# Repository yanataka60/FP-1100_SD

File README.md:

# CASIO FP-1100にSD-Cardとのロード、セーブ機能

　CASIO FP-1100でCMTの代わりにSD-CARDからロード、セーブを実現するものです。

　FP-1000は所有していないので試していませんが、動作すると思います。

　SDから読み込めるCMTのファイル形式はEMUで一般的なWAV、CASには対応していません。bugfire2009さんのDumpListEditorを使ってバイナリ形式に変換したものを使います。

　機械語 -> 各モデル固有ヘッダ付きBINファイル、拡張子は.bin

　BASIC -> BASファイル、拡張子は.bas

　CMTからの読み込み実行に数分掛かっていたゲームも数十秒で実行できます。

　ただし、CMT用プログラムのすべてがSD対応となるわけではありません。特に市販ゲームはCMT読み込みに独自ルーチンを使っているものもあるため、SD対応は不明です。

　なお、Arduino、ROMへ書き込むための機器が別途必要となります。

## 回路図
　KiCadフォルダ内のFP-1100_SD.PDFを参照してください。

[回路図](https://github.com/yanataka60/FP-1100_SD/blob/main/Kicad/FP-1100_SD.PDF)

## 部品
|番号|品名|数量|備考|
| ------------ | ------------ | ------------ | ------------ |
||J3,J4のいずれか|||
|J3|Micro_SD_Card_Kit|1|秋月電子通商 AE-microSD-LLCNV (注1)|
|J4|MicroSD Card Adapter|1|Arduino等に使われる5V電源に対応したもの(注2)|
|U1-U3|74LS04|3||
|U4-U5|74LS02|2||
|U6-U8|74LS30|3||
|U10|8255|1||
|U11|Arduino_Pro_Mini_5V|1|Atmega328版を使用 168版は不可。(注3)|
|U12|74LS32|1||
|U13|74LS244|1||
|U14|ROM 27256/29C256又は27512/27C512相当品|1|入手しやすいものでOK、28C256は不可|
|C1-C10,C12,C13|積層セラミックコンデンサ 0.1uF|12||
|C11|電解コンデンサ 16v100uF|1||
|S1|3Pin ピンヘッダーとジャンパーピン又は3Pスライドスイッチ|1|秋月電子通商 SS12D01G4など|

### 注1)秋月電子通商　AE-microSD-LLCNVのJ1ジャンパはショートしてください。

### 注2)MicroSD Card Adapterを使う場合

J4に取り付けます。

MicroSD Card Adapterについているピンヘッダを除去してハンダ付けするのが一番確実ですが、J2の穴にMicroSD Card Adapterをぴったりと押しつけ、裏から多めにハンダを流し込むことでハンダ付けをする方法もあります。なお、この方法の時にはしっかりハンダ付けが出来たかテスターで導通を確認しておいた方が安心です。

ハンダ付けに自信のない方はJ1の秋月電子通商　AE-microSD-LLCNVをお使いください。AE-microSD-LLCNVならパワーLED、アクセスLEDが付いています。

### 注3)Arduino Pro MiniはA4、A5ピンも使っています。

## FP-1100_SDをスロットに入れずに外付けとして使いたい場合のみ
　J2ピンヘッダを取り付けます。また、スロットからケーブルを引き出す基板が必要ですのでFP-1100_SD基板がもう一枚必要です。

|番号|品名|数量|備考|
| ------------ | ------------ | ------------ | ------------ |
|J2|2x25Pinコネクタ|1|秋月電子通商 PH-2x40SGなど|
||FP-1100_SD基板|1||
||2.54mmピッチ2x25Pinフラットケーブル|1|FP-1100の拡張スロットは2x28Pinですが、2x25Pinが使えます|

## 取り付け
　FP-1100本体後ろのスロットに挿入します。

　スロットにガイド等が無いためスロットの奥を覗き込みながら挿入します。

　基板の下に10～12mmの隙間が空くようにネジやスペーサーなどを取り付け、カードエッジコネクタと高さを合わせると挿入しやすくなります。

　外すときには基板のねじ穴にドライバー等を差し込んでひねるようにすれば取り外しやすいです。

　STLフォルダに基板を載せられるトレイの3Dデータを置いたので出力して使うと抜き差しが楽になります。

　標準はSLOT0ですが、SLOT1で使うときは起動後にSLコマンドでSLOT1を指定してください。

### FP-1100_SDをスロットに入れずに外付けとしてフラットケーブルによる接続
　J2コネクタ1Pinを示す基板上の△印にフラットケーブルの1Pinを示す△印を合わせてフラットケーブルを挿入します。

　FP-1100の拡張スロットは2x28Pinですが、2x25Pinフラットケーブルが使えます。

.JPG)
.JPG)
.JPG)

## ROMへの書込み
　Z80フォルダ内のRAMPACK1.binをROMライター(TL866II Plus等)を使って27256又は27512に書き込みます。

　実際に使用しているのは16KByte分(16Kx8)です。

　FP-1100_SDのROMはFP-1100からはRAMパックとして扱われます。(FP-1100から書き込みはできません。)

　本物のRAMパック、ROMパックともハードウェア的には併用可能なはずですが、現物を所有していないため動作検証は行っていません。

### 2025.8.12 FP-1100_SD以外のPACKをSLOTに挿入して同時に使用している場合にSDにアクセスできなくなるバグを発見しました。
　現在バージョンは修正済みですが、旧バージョンROMの方はZ80フォルダ内のPATCH.binをSDにコピーし、SDF8(SDE8)を実行直後にSDアクセスメニューに入り、読み込み実行すれば修正されます。

## RAMPACK1.binに登録されているファイル
　RAMPACK1.binに登録されているファイルは次の4つになります。

|ファイル名|種類|
| ------------ | ------------ |
|SDF8|BASIC|
|SDE8|BASIC|
|BOOTF8|BINARY|
|BOOTE8|BINARY|

　また、RAMPACK1.binへのファイル登録はTAKEDAさんのEMU eFP-1100で行っており、fp1100.exeと同じフォルダに置くことでeFP-1100からは「PACK0:」として読み書き出来ます。

## Arduinoプログラム
　Arduino IDEを使ってArduinoフォルダのFP-1100_SDフォルダ内FP-1100_SD.inoを書き込みます。

　SdFatライブラリを使用しているのでArduino IDEメニューのライブラリの管理からライブラリマネージャを立ち上げて「SdFat」をインストールしてください。

　「SdFat」で検索すれば見つかります。「SdFat」と「SdFat - Adafruit Fork」が見つかりますが「SdFat」のほうを使っています。

注)Arduinoを基板に直付けしている場合、Arduinoプログラムを書き込むときは、FP-1100本体とは接続を外し、U3 74LS04を外したうえで書き込んでください。

## SD-CARD
　出来れば8GB以下のSDカードを用意してください。

　ArduinoのSdFatライブラリは、SD規格(最大2GB)、SDHC規格(2GB～32GB)に対応していますが、SDXC規格(32GB～2TB)には対応していません。

　また、SDHC規格のSDカードであっても32GB、16GBは相性により動作しないものがあるようです。

　FAT16又はFAT32が認識できます。NTFSは認識できません。

## 操作方法
　起動直後に「RUN"PACK0:SDF8"」を実行してSDアクセスルーチンの読込、初期化の実行を行います。

　SDアクセスルーチンをF800h～FFFChに読み込む「SDF8」とE800h～EFF2hに読み込む「SDE8」の２種類を用意していますが、基本的には「SDF8」を使い、F000h～FFFFhへプログラムをロードしたいときだけ「SDE8」を使ってください。

　「SDE8」を使うときは、「RUN"PACK0:SDE8"」を実行します。

　SDアクセスメニューを表示するにはCALL&HF800(CALL&HE800)を実行しますが、F7ファンクションキーに登録してありますのでF7ファンクションキーを押しても大丈夫です。

#### 扱えるファイル
bugfire2009さんのDumpListEditorを使ってバイナリ形式に変換したものを使います。

扱う機種をFP-1100に変更したうえで変換します。

##### 機械語 -> 「BINファイル書出し(各モデル固有ヘッダ付き)」で保存、拡張子は.bin

##### BASIC -> 「BASファイル書出し」で保存、拡張子は.bas

### コマンド
　コマンド入力時にBSキー又は左カーソルキーで直前に入力した文字を訂正できます。

　CLR、HOME、上・下・右カーソルキーは画面が乱れるだけで入力文字の訂正は出来ません。

#### 2025.8.12 BASICプログラムを実行した後にSDアクセスメニューを実行するとコマンドを入力できなくなる場合があるようです。
　原因を調査中ですが、回避方法は以下になります。

　コマンドが入力できない状態の時はBREAKキーを押すことでBASICに戻れます。

　LISTコマンドを一回実行してください。途中でBREAKしても大丈夫です。これでSDアクセスメニューを実行しても入力できる状態に戻ります。

#### SD[RETURN]又はSD 文字列[RETURN]
　文字列を入力せずにSD[RETURN]のみ入力するとSD-CARDルートディレクトリにあるファイルの一覧を表示します。

　文字列を付けて入力すればSD-CARDルートディレクトリにあるその文字列から始まるファイルの一覧を表示します。
　10件表示したところで指示待ちになるのでESCキーで終了、Bキー又はBSキーで前の10件に戻ります。それ以外のキーで次の10件を表示します。

　LOADしたいファイルを見つけたら左端の数字のキーを押せばLOADされます。

　BASICプログラムか、機械語プログラムかは自動で判断します。

　なお、F7FFh以降へ機械語プログラムがLOADされた場合、次の三段階の挙動となります。

　1)～F9ACh:機械語プログラムをLOAD後は、SM,SB,SLコマンドが使用できなくなります。LM,LG,LB,SD,G,Q,Bコマンドは使用できます。

　2)～FDDEh:機械語プログラムをLOAD後は、G,Q,Bのみ使えます。SD,LMコマンドでLOADした後、Gコマンドでの実行は可能です。

　3)～FF59h:機械語プログラムをLOAD後は、すべてのコマンドが使えません。FDDFh以降までLOADされた場合は強制的に実行番地にジャンプを試みます。

　表示される順番は、登録順となりファイル名アルファベッド順などのソートした順で表示することはできません。

##### 例)
　　SD[RETURN]

　　SD S[RETURN]

　　SD SP[RETURN]

#### LM DOSファイル名[RETURN]
　指定したDOSフィル名の機械語プログラムをSD-CARDからLOADします。

　拡張子が「bin」であるファイルだけが対象でファイル名の最後が「.BIN」でない場合には自動的に付加されます。
　読み込める機械語プログラムの範囲は通常F7FFhまでとなります。F000h～FFFFhへ機械語プログラムをLOADしたいときは「SDE8」を使用してください。

　なお、F7FFh以降へ機械語プログラムがLOADされた場合、次の三段階の挙動となります。

　1)～F9ACh:機械語プログラムをLOAD後は、SM,SB,SLコマンドが使用できなくなります。LM,LG,LB,SD,G,Q,Bコマンドは使用できます。

　2)～FDDEh:機械語プログラムをLOAD後は、G,Q,Bのみ使えます。SD,LMコマンドでLOADした後、Gコマンドでの実行は可能です。

　3)～FF59h:機械語プログラムをLOAD後は、すべてのコマンドが使えません。FDDFh以降までLOADされた場合は強制的に実行番地にジャンプを試みます。

##### 例)
　　LM TEST[RETURN] -> DOSファイル名「TEST.BIN」を読み込みます。

　　LM TEST.BIN[RETURN] -> DOSファイル名「TEST.BIN」を読み込みます。

　　LM TEST.BAS[RETURN] -> DOSファイル名「TEST.BAS.BIN」を読み込みます。

#### LG DOSファイル名[RETURN]
　指定したDOSフィル名の機械語プログラムをSD-CARDからLOADした後、実行開始アドレスへジャンプします。

　LOAD後そのまま実行するのでFF64hまでLOADしても大丈夫です。

　LOADした後、実行開始アドレスへジャンプする以外はLMコマンドと同じです。

#### LB DOSファイル名[RETURN]
　現在選択しているPROGエリアに指定したDOSフィル名のBASICプログラムをSD-CARDからLOADします。

　LOADするPROGエリアを切り替えたい場合にはSDメニューに入る前に切り替えておいてください。

　拡張子が「bas」であるファイルだけが対象でファイル名の最後が「.BAS」でない場合には自動的に付加されます。

##### 例)
　　LB TEST[RETURN] -> DOSファイル名「TEST.BAS」を読み込みます。

　　LB TEST.BAS[RETURN] -> DOSファイル名「TEST.BAS」を読み込みます。

　　LB TEST.BIN[RETURN] -> DOSファイル名「TEST.BIN.BAS」を読み込みます。

#### SM XXXX,YYYY,ZZZZ,DOSファイル名[RETURN]　(XXXX,YYYY,ZZZZは16進数4桁を表す文字列)
　XXXX番地からYYYY番地までの機械語プログラムを実行番地ZZZZとして指定したDOSフィル名でSD-CARDにSAVEします。

　拡張子の指定「.bin」は省略することが出来、ファイル名の最後が「.BIN」でない場合には自動的に付加されます。

##### 例)
　　SM B000,BFFF,B000,TEST[RETURN] -> B000h～BFFFhまでを実行番地B000hとしてDOSファイル名「TEST.BIN」でSAVEします。

　　SM B000,BFFF,B000,TEST.BIN[RETURN] -> B000h～BFFFhまでを実行番地B000hとしてDOSファイル名「TEST.BIN」でSAVEします。

　　SM B000,BFFF,B000,TEST.BAS[RETURN] -> B000h～BFFFhまでを実行番地B000hとしてDOSファイル名「TEST.BAS.BIN」でSAVEします。

#### SB DOSファイル名[RETURN]
　現在選択しているPROGエリアのBASICプログラムを指定したDOSフィル名でSD-CARDにSAVEします。

　SAVEするPROGエリアを切り替えたい場合にはSDメニューに入る前に切り替えておいてください。

　拡張子の指定「.bas」は省略することが出来、ファイル名の最後が「.BAS」でない場合には自動的に付加されます。

##### 例)
　　SB TEST[RETURN] -> DOSファイル名「TEST.BAS」でSAVEします。

　　SB TEST.BAS[RETURN] -> DOSファイル名「TEST.BAS」でSAVEします。

　　SB TEST.BIN[RETURN] -> DOSファイル名「TEST.BIN.BAS」でSAVEします。

#### G[RETURN]又はG 16進数4桁[RETURN]
　Gだけの場合は、直前にLOADした機械語プログラムの実行番地へジャンプします。

　16進数4桁を指定した場合は16進数4桁が表すアドレスにジャンプします。

　Gの後ろに空白があっても無くても構いません。

#### SL[RETURN]
　入力待ちになるので0又は1キーでSLOT番号を入力します。0,1以外を入力した場合は再度入力待ちになります。

　FP-1100_SD初期化直後はSLOT0になっていますのでFP-1100_SDをSLOT1に挿入して使う場合には切り替えてください。

#### B[RETURN]又はQ[RETURN]
　BASICに復帰します。

### BASICプログラム中から機械語プログラムをLOADする
　BASICプログラム中に「CALL &HF803:REM ファイル名」と記述することで機械語プログラムをLOAD出来ます。

　ファイル名はSDカードに保存されているファイル名です。拡張子はつけてもつけなくても構いません。

　LOAD出来るのはF7FFhまでです。(clear文を修正すれば最大FA3Fhまで可能です)

##### 例)

30 CALL &HF803:REM TRAFFIC CONTROL.bin

## 操作上の注意
　電源を入れたままSD-CARDの抜き差しをする場合又は「SD-CARD INITIALIZE ERROR」と表示されたときは、SD-CARDを挿入後、SD、LM、LBコマンド等でSD-CARDに3回ほどアクセスすれば復旧します。

　SD-CARDの抜き差しは電源を切った状態で行うほうがより確実です。

## 謝辞
　基板の作成に当たり以下のデータを使わせていただきました。ありがとうございました。

　Arduino Pro Mini

　　https://github.com/g200kg/kicad-lib-arduino

　AE-microSD-LLCNV

　　https://github.com/kuninet/PC-8001-SD-8kRAM

　FP-1100の資料を提供いただいたPro Nyan@Nyan4Pro様、ありがとうございました。

## 追記
2025.7.11 SDコマンドでF9A9hを超えて機械語プログラムをLOADした時の挙動にバグがあったので修正。FDDAhを超えるLOADの場合は強制的に実行番地へジャンプすることに修正。

2025.7.13 BASICプログラムLOAD時のAREA OVERエラー表示のバグを修正。

2025.7.30 BASICプログラム未入力でSAVEしようとしたときに'Basic Program Nothing!'と表示した後Arduinoが応答しなくなるバグを修正。それに伴ってF7FFh以降へ機械語プログラムがLOADされた場合の限界アドレスが変動。

2025.8.6 BASICプログラム中から機械語プログラムをLOADする方法の記述が抜けていたので追記。

2025.8.12 FP-1100_SD以外のPACKを同時に使うときにはSLOTを再指定する必要があったので修正。BASICプログラムを実行した後にSDアクセスメニューを実行するとコマンドを入力できなくなる場合の回避方法を記述。

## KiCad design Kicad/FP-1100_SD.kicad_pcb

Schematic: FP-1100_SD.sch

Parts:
C1, C2, C3, C4, C5, C6, C7, C8, C9, C10, C12, C13: 0.1uF; C_Rect_L4.0mm_W2.5mm_P2.50mm
C11: 100uF; CP_Radial_D5.0mm_P2.50mm
J1: FP-1100_BUS; BUS_56Pin
J2: FP-1100_BUS; PinSocket_2x25_P2.54mm_Vertical
J3: Micro_SD_Card_Kit; AE-microSD-LLCNV
J4: MicroSD Card Adapter; PinHeader_1x06_P2.54mm_Vertical
S1: 27512/27256; PinHeader_1x03_P2.54mm_Vertical
U1, U2, U3: 74LS04; DIP-14_W7.62mm_LongPads
U4, U5: 74LS02; DIP-14_W7.62mm_LongPads
U6, U7, U8: 74LS30; DIP-14_W7.62mm_LongPads
U10: 8255; DIP-40_W15.24mm_LongPads
U11: Arduino_Pro_Mini_5V; Arduino_Pro_Mini
U12: 74LS32; DIP-14_W7.62mm_LongPads
U13: 74LS244; DIP-20_W7.62mm_LongPads
U14: 27512; DIP-28_W15.24mm

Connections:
+5V: C1.2, C2.2, C3.2, C4.2, C5.2, C6.2, C7.2, C8.2, C9.1, C10.1, C11.1, C12.2, C13.2, J1.a1, J1.a2, J1.a26, J1.a27, J2.a1, J2.a2, J3.1 (5V), J4.2, S1.3, U1.14 (VCC), U2.14 (VCC), U3.14 (VCC), U4.14 (VCC), U5.14 (VCC), U6.14 (VCC), U7.14 (VCC), U8.5, U8.6, U8.11, U8.12, U8.14 (VCC), U10.26 (VCC), U11.21 (VCC), U12.14 (VCC), U13.2 (I0a), U13.20 (VCC), U14.28 (VCC)
/+12V: J1.a3, J1.b3, J2.a3, J2.b3
/-5V: J1.b25, J2.b25
/-12V: J1.a25, J2.a25
/A0: U1.2, U10.9 (A0), U14.10 (A0)
/A1: U1.4, U10.8 (A1), U14.9 (A1)
/A2: U1.6, U14.8 (A2)
/A3: U1.8, U14.7 (A3)
/A4: U1.10, U14.6 (A4)
/A5: U1.12, U14.5 (A5)
/A6: U2.2, U14.4 (A6)
/A7: U2.4, U14.3 (A7)
/A8: U2.6, U14.25 (A8)
/A9: U2.8, U14.24 (A9)
/A10: U2.10, U14.21 (A10)
/A11: U2.12, U14.23 (A11)
/A12: U3.2, U14.2 (A12)
/A13: U3.4, U6.4, U14.26 (A13)
/A14: U3.6, U6.5
/A15: U3.8, U6.6
/CLOCK: J1.b4, J2.b4
/CS: J3.8 (CS), J4.6, U11.13 (~~D10)
/D0: J1.a13, J2.a13, U10.34 (D0), U13.18 (O0a), U14.11 (D0)
/D1: J1.b13, J2.b13, U10.33 (D1), U13.16 (O1a), U14.12 (D1)
/D2: J1.a14, J2.a14, U10.32 (D2), U13.14 (O2a), U14.13 (D2)
/D3: J1.b14, J2.b14, U10.31 (D3), U13.12 (O3a), U14.15 (D3)
/D4: J1.a15, J2.a15, U10.30 (D4), U13.9 (O0b), U14.16 (D4)
/D5: J1.b15, J2.b15, U10.29 (D5), U13.7 (O1b), U14.17 (D5)
/D6: J1.a16, J2.a16, U10.28 (D6), U13.5 (O2b), U14.18 (D6)
/D7: J1.b16, J2.b16, U10.27 (D7), U13.3 (O3b), U14.19 (D7)
/MISO: J3.6 (DAT), J4.3, U11.15 (D12)
/MOSI: J3.7 (CMD), J4.4, U11.14 (~~D11)
/PSL: U4.10, U6.11, U8.3
/REQD: U4.13, U6.12, U8.4
/SCK: J3.5 (CLK), J4.5, U11.16 (D13)
/~A0: J1.a17, J2.a17, U1.1
/~A1: J1.b17, J2.b17, U1.3
/~A2: J1.a18, J2.a18, U1.5, U7.1
/~A3: J1.b18, J2.b18, U1.9, U7.2
/~A4: J1.a19, J2.a19, U1.11, U7.3
/~A5: J1.b19, J2.b19, U1.13, U7.4
/~A6: J1.a20, J2.a20, U2.1, U7.5
/~A7: J1.b20, J2.b20, U2.3, U7.6
/~A8: J1.a21, J2.a21, U2.5, U7.11
/~A9: J1.b21, J2.b21, U2.9, U7.12
/~A10: J1.a22, J2.a22, U2.11, U6.1
/~A11: J1.b22, J2.b22, U2.13, U6.2
/~A12: J1.a23, J2.a23, U3.1, U6.3
/~A13: J1.b23, J2.b23, U3.3
/~A14: J1.a24, J2.a24, U3.5, U8.1
/~A15: J1.b24, J2.b24, U3.9, U8.2
/~BSL: J1.a5, J2.a5
/~CS: J1.a8, J2.a8, U12.4
/~INTA: J1.a11, J2.a11
/~INTB: J1.b11, J2.b11
/~INTC: J1.a12, J2.a12
/~INTD: J1.b12, J2.b12
/~LPS: J1.b10, J2.b10
/~NMI: J1.a10, J2.a10
/~PSL: J1.a4, J2.a4, U4.8, U4.9, U12.10
/~RD: J1.a7, J2.a7, U4.2, U12.5
/~REQ: J1.a6, J2.a6
/~REQD: J1.b6, J2.b6, U4.3, U4.11, U4.12, U5.9, U12.9
/~RESET: J1.b5, J2.b5, U3.11
/~WR: J1.b7, J2.b7, U5.8
GND: C1.1, C2.1, C3.1, C4.1, C5.1, C6.1, C7.1, C8.1, C9.2, C10.2, C11.2, C12.1, C13.1, J1.b1, J1.b2, J1.b26, J1.b27, J2.b1, J2.b2, J3.4 (GND), J4.1, S1.1, U1.7 (GND), U2.7 (GND), U3.7 (GND), U4.7 (GND), U5.7 (GND), U6.7 (GND), U7.7 (GND), U8.7 (GND), U10.7 (GND), U11.23 (GND), U12.7 (GND), U12.12, U12.13, U13.4 (I1a), U13.6 (I2a), U13.8 (I3a), U13.10 (GND), U13.11 (I0b), U13.13 (I1b), U13.15 (I2b), U13.17 (I3b), U14.14 (GND), U14.27 (A14)
unnamed: S1.2, U14.1 (A15)
unnamed: U4.1, U4.5, U4.6
unnamed: U5.1, U5.5, U5.6
unnamed: U5.2, U6.8
unnamed: U5.3, U7.8
unnamed: U5.10, U5.11, U5.12
unnamed: U10.1 (PA3), U11.A5
unnamed: U10.2 (PA2), U11.A4
unnamed: U10.3 (PA1), U11.20 (D17/A3)
unnamed: U10.4 (PA0), U11.19 (D16/A2)
unnamed: U4.4, U10.5 (~RD~), U14.22 (~OE)
unnamed: U5.4, U10.6 (~CS~)
unnamed: U10.10 (PC7), U11.17 (D14/A0)
unnamed: U10.16 (PC2), U11.18 (D15/A1)
unnamed: U10.18 (PB0), U11.5 (D2)
unnamed: U10.19 (PB1), U11.6 (~~D3)
unnamed: U10.20 (PB2), U11.7 (D4)
unnamed: U10.21 (PB3), U11.8 (~~D5)
unnamed: U10.22 (PB4), U11.9 (~~D6)
unnamed: U10.23 (PB5), U11.10 (D7)
unnamed: U10.24 (PB6), U11.11 (D8)
unnamed: U10.25 (PB7), U11.12 (~~D9)
unnamed: U3.10, U3.13, U10.35 (RESET)
unnamed: U5.13, U10.36 (~WR~)
unnamed: U3.12, U11.3 (RST)
unnamed: U12.1, U12.6
unnamed: U12.2, U12.8
unnamed: U12.3, U13.1 (OEa), U13.19 (OEb)
unnamed: U8.8, U14.20 (~CE)

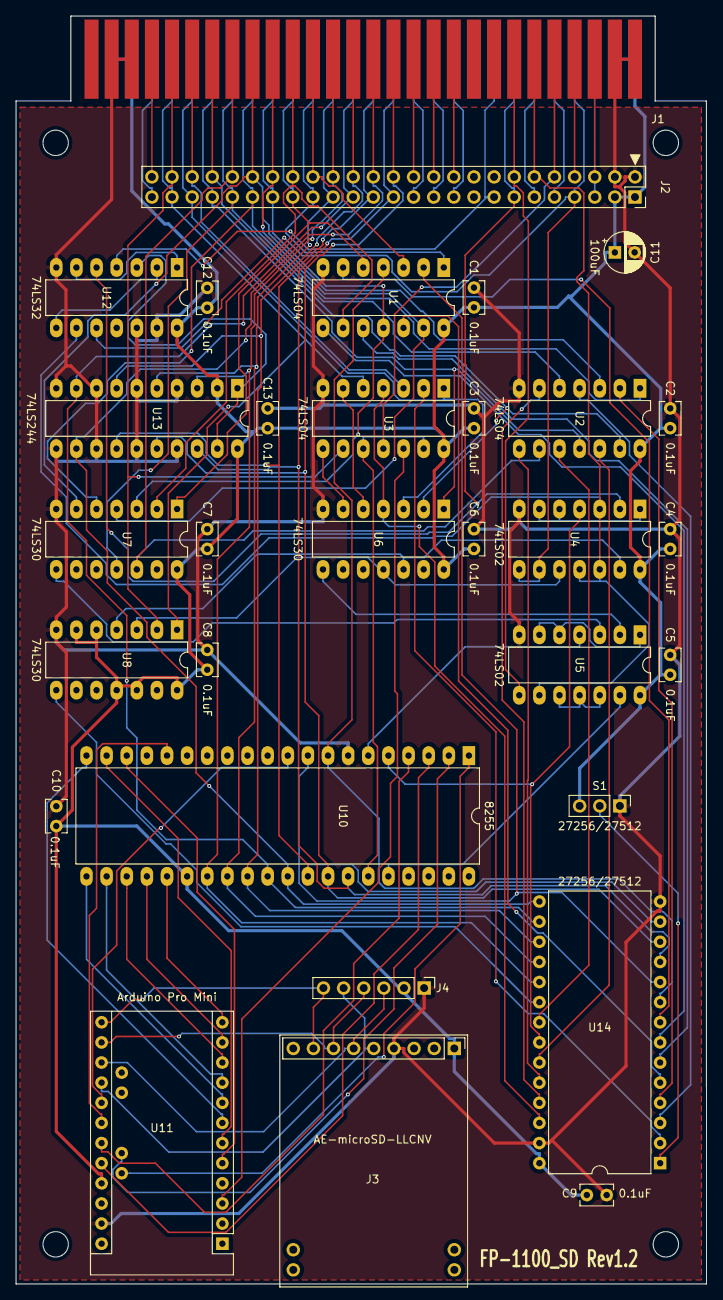
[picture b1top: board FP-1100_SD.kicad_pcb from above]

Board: 2 copper layers, 87.1 x 160.0 mm, 35 parts (0 on the bottom side), 95 nets.

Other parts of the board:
MH1, MH2, MH3, MH4: MountingHole_3.2mm_M3
